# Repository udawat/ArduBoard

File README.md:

ArduBoard
=========

ArduBoard is an Arduino Compatible Board designed by keeping in mind easy interfacing of I2C devices, on-board 5V, 3.3V Voltage Regulators and FTDI compatibility in a compact form-factor which is also BreadBoard Compatible!

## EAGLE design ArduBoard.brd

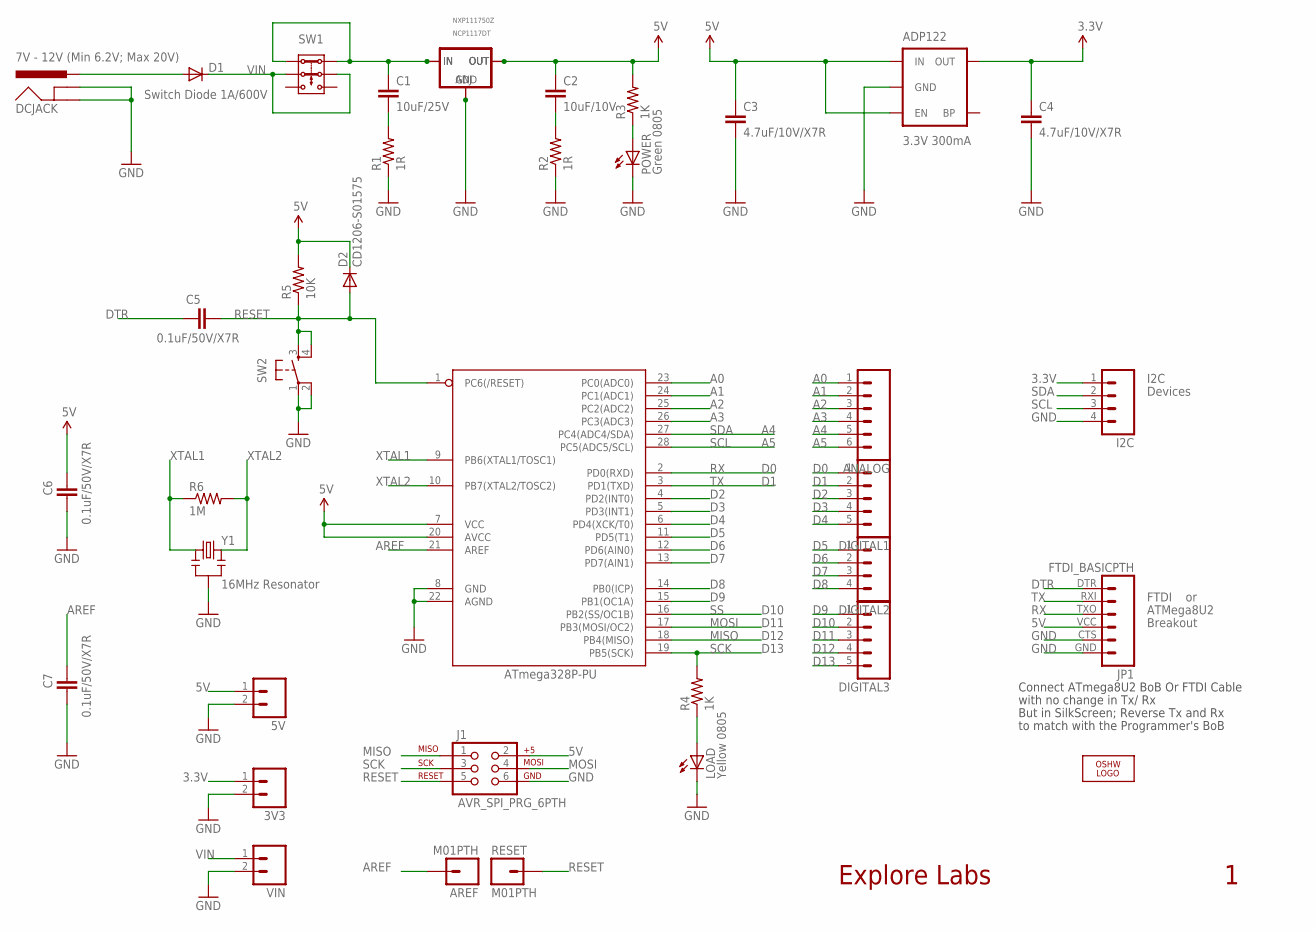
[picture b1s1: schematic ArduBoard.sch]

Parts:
3V3, 5V: M02PTH; 1X02
ADP122: 3.3V 300mA; SOT23-5
ANALOG: M06SIP; 1X06
AREF: M01PTH; 1X01
ATMEGA328P-PU: AVR-MEGA8-PPTH; DIL28-3
C1: 10uF/25V; 1206
C2: 10uF/10V; 1206
C3, C4: 4.7uF/10V/X7R; 0805
C5, C6, C7: 0.1uF/50V/X7R; 0805
D1: Switch Diode 1A/600V; DO-214AC
D2: CD1206-S01575; MINIMELF
DCJACK: POWER_JACKPTH; POWER_JACK_PTH
DIGITAL1, DIGITAL3: M05PTH; 1X05
DIGITAL2: M04PTH; 1X04
I2C: M04PTH; 1X04
IC1: V_REG_MIC2920NXPNX1117C50Z; SOT223
J1: AVR_SPI_PRG_6PTH; 2X3
JP1: FTDI_BASICPTH; FTDI_BASIC
LOAD: Yellow 0805; CHIP-LED0805
LOGO1: OSHW_LOGO_FILLX0150-NT; OSHW_FILLX150_NOTEXT
POWER: Green 0805; CHIPLED_0805
R1, R2: 1R; 0603-RES
R3, R4: 1K; 0603-RES
R5: 10K; 0603-RES
R6: 1M; 0805
RESET: M01PTH; 1X01
SW1: DPDTELEMENT14; MS
SW2: TAC_SWITCHPTH; TACTILE-PTH
U1: V_REG_317DPACK; V-REG_DPACK
VIN: M02PTH; 1X02
Y1: 16MHz Resonator; RESONATOR-SMD

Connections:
3.3V: 3V3.1, ADP122.5 (OUT), C4.1, I2C.1
5V: 5V.1, ADP122.1 (IN), ADP122.3 (EN), ATMEGA328P-PU.7 (VCC), ATMEGA328P-PU.20 (AVCC), C2.1, C3.1, C6.2, D2.C, IC1.4 (OUT), J1.2, JP1.VCC (4), R3.2, R5.2, U1.4 (OUT)
A0: ANALOG.1, ATMEGA328P-PU.23 (PC0(ADC0))
A1: ANALOG.2, ATMEGA328P-PU.24 (PC1(ADC1))
A2: ANALOG.3, ATMEGA328P-PU.25 (PC2(ADC2))
A3: ANALOG.4, ATMEGA328P-PU.26 (PC3(ADC3))
AREF: AREF.1, ATMEGA328P-PU.21 (AREF), C7.2
D2: ATMEGA328P-PU.4 (PD2(INT0)), DIGITAL1.3
D3: ATMEGA328P-PU.5 (PD3(INT1)), DIGITAL1.4
D4: ATMEGA328P-PU.6 (PD4(XCK/T0)), DIGITAL1.5
D5: ATMEGA328P-PU.11 (PD5(T1)), DIGITAL2.1
D6: ATMEGA328P-PU.12 (PD6(AIN0)), DIGITAL2.2
D7: ATMEGA328P-PU.13 (PD7(AIN1)), DIGITAL2.3
D8: ATMEGA328P-PU.14 (PB0(ICP)), DIGITAL2.4
D9: ATMEGA328P-PU.15 (PB1(OC1A)), DIGITAL3.1
DTR: C5.1, JP1.DTR (1)
GND: 3V3.2, 5V.2, ADP122.2 (GND), ATMEGA328P-PU.8 (GND), ATMEGA328P-PU.22 (AGND), C3.2, C4.2, C6.1, C7.1, DCJACK.GND, DCJACK.GNDBREAK, I2C.4, IC1.1 (GND), J1.6, JP1.CTS (5), JP1.GND (6), LOAD.C, POWER.C, R1.1, R2.1, SW2.1, SW2.2, U1.1 (ADJ), VIN.2, Y1.2
MISO: ATMEGA328P-PU.18 (PB4(MISO)), DIGITAL3.4, J1.1
MOSI: ATMEGA328P-PU.17 (PB3(MOSI/OC2)), DIGITAL3.3, J1.4
unnamed: C1.2, R1.2
unnamed: C1.1, IC1.3 (IN), SW1.P$1 (1.2), SW1.P$2 (1.1), U1.3 (IN)
unnamed: C2.2, R2.2
unnamed: POWER.A, R3.1
unnamed: LOAD.A, R4.1
unnamed: D1.A, DCJACK.PWR
RESET: ATMEGA328P-PU.1 (PC6(/RESET)), C5.2, D2.A, J1.5, R5.1, RESET.1, SW2.3, SW2.4
RX: ATMEGA328P-PU.2 (PD0(RXD)), DIGITAL1.1, JP1.TXO (3)
SCK: ATMEGA328P-PU.19 (PB5(SCK)), DIGITAL3.5, J1.3, R4.2
SCL: ANALOG.6, ATMEGA328P-PU.28 (PC5(ADC5/SCL)), I2C.3
SDA: ANALOG.5, ATMEGA328P-PU.27 (PC4(ADC4/SDA)), I2C.2
SS: ATMEGA328P-PU.16 (PB2(SS/OC1B)), DIGITAL3.2
TX: ATMEGA328P-PU.3 (PD1(TXD)), DIGITAL1.2, JP1.RXI (2)
VIN: D1.C, SW1.P$3 (2.1), SW1.P$4 (2.2), VIN.1
XTAL1: ATMEGA328P-PU.9 (PB6(XTAL1/TOSC1)), R6.1, Y1.1
XTAL2: ATMEGA328P-PU.10 (PB7(XTAL2/TOSC2)), R6.2, Y1.3

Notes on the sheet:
ATMega8U2
Breakout
FTDI
I2C
Devices
ATmega328P-PU
7V - 12V (Min 6.2V; Max 20V)
Explore Labs
Connect ATmega8U2 BoB Or FTDI Cable
with no change in Tx/ Rx
But in SilkScreen; Reverse Tx and Rx
to match with the Programmer's BoB
D10
D11
D12
D13
NXP111750Z
NCP1117DT

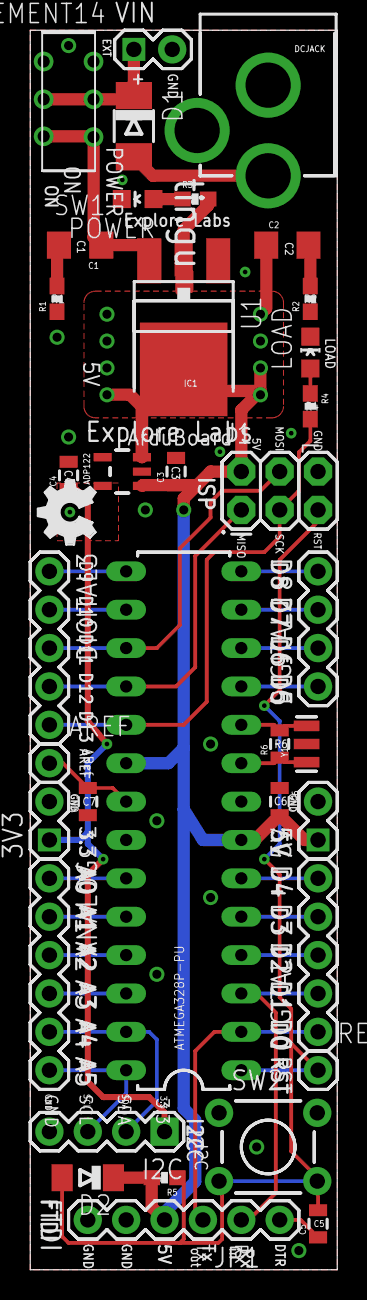
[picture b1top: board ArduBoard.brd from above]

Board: 2 copper layers, 20.3 x 82.0 mm, 38 parts (0 on the bottom side), 35 nets.

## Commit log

2012-11-23 initial commit for v1
2012-11-23 moving things around
2012-11-23 swap
2012-11-23 finalizing...

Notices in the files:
parts and their libraries:
SparkFun-DigitalIC: Licensing: CC v3.0 Share-Alike You are welcome to use this library for commercial purposes.
SparkFun-Aesthetics: Released under the Creative Commons
SparkFun-Aesthetics: http://creativecommons.org/licenses/by-sa/3.0
